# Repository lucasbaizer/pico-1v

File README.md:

# PICO 1V IS WIP

The PCB for Pico 1V is still in progress. Don't use it!

# Pico 1V

Pico 1V is an RP2040 board with the following additions/changes from the official Raspberry Pi Pico board:

* Switchable 1.8V/3.3V GPIO.
* A power LED.
* A reset button.
* A USB-C port instead of a Micro-B port.

Pico 1V is sill pin-compatible with the official Raspberry Pi Pico board, so you can use Pico 1V as a drop-in replacement for your existing Pico board.

## Acknowledgements

The schematic for Pico 1V was originally based on [Mitayi-Pico-D1](https://github.com/CIRCUITSTATE/Mitayi-Pico-D1), and the PCB for Pico 1V is from scratch.
Some of the components in the Pico 1V schematic are nearly unchanged from the Mitayi-Pico-D1 schematic.
Huge thanks to CIRCUITSTATE for open-sourcing Mitayi-Pico-D1, it was very helpful for this.

The voltage-switching implementation is based on the method described in [xenia's fantastic blog post](https://blog.awoo.systems/posts/2024-07-27-rp2040-low-voltage-operation).

## License

This project is licensed under the [MIT license](./LICENSE).

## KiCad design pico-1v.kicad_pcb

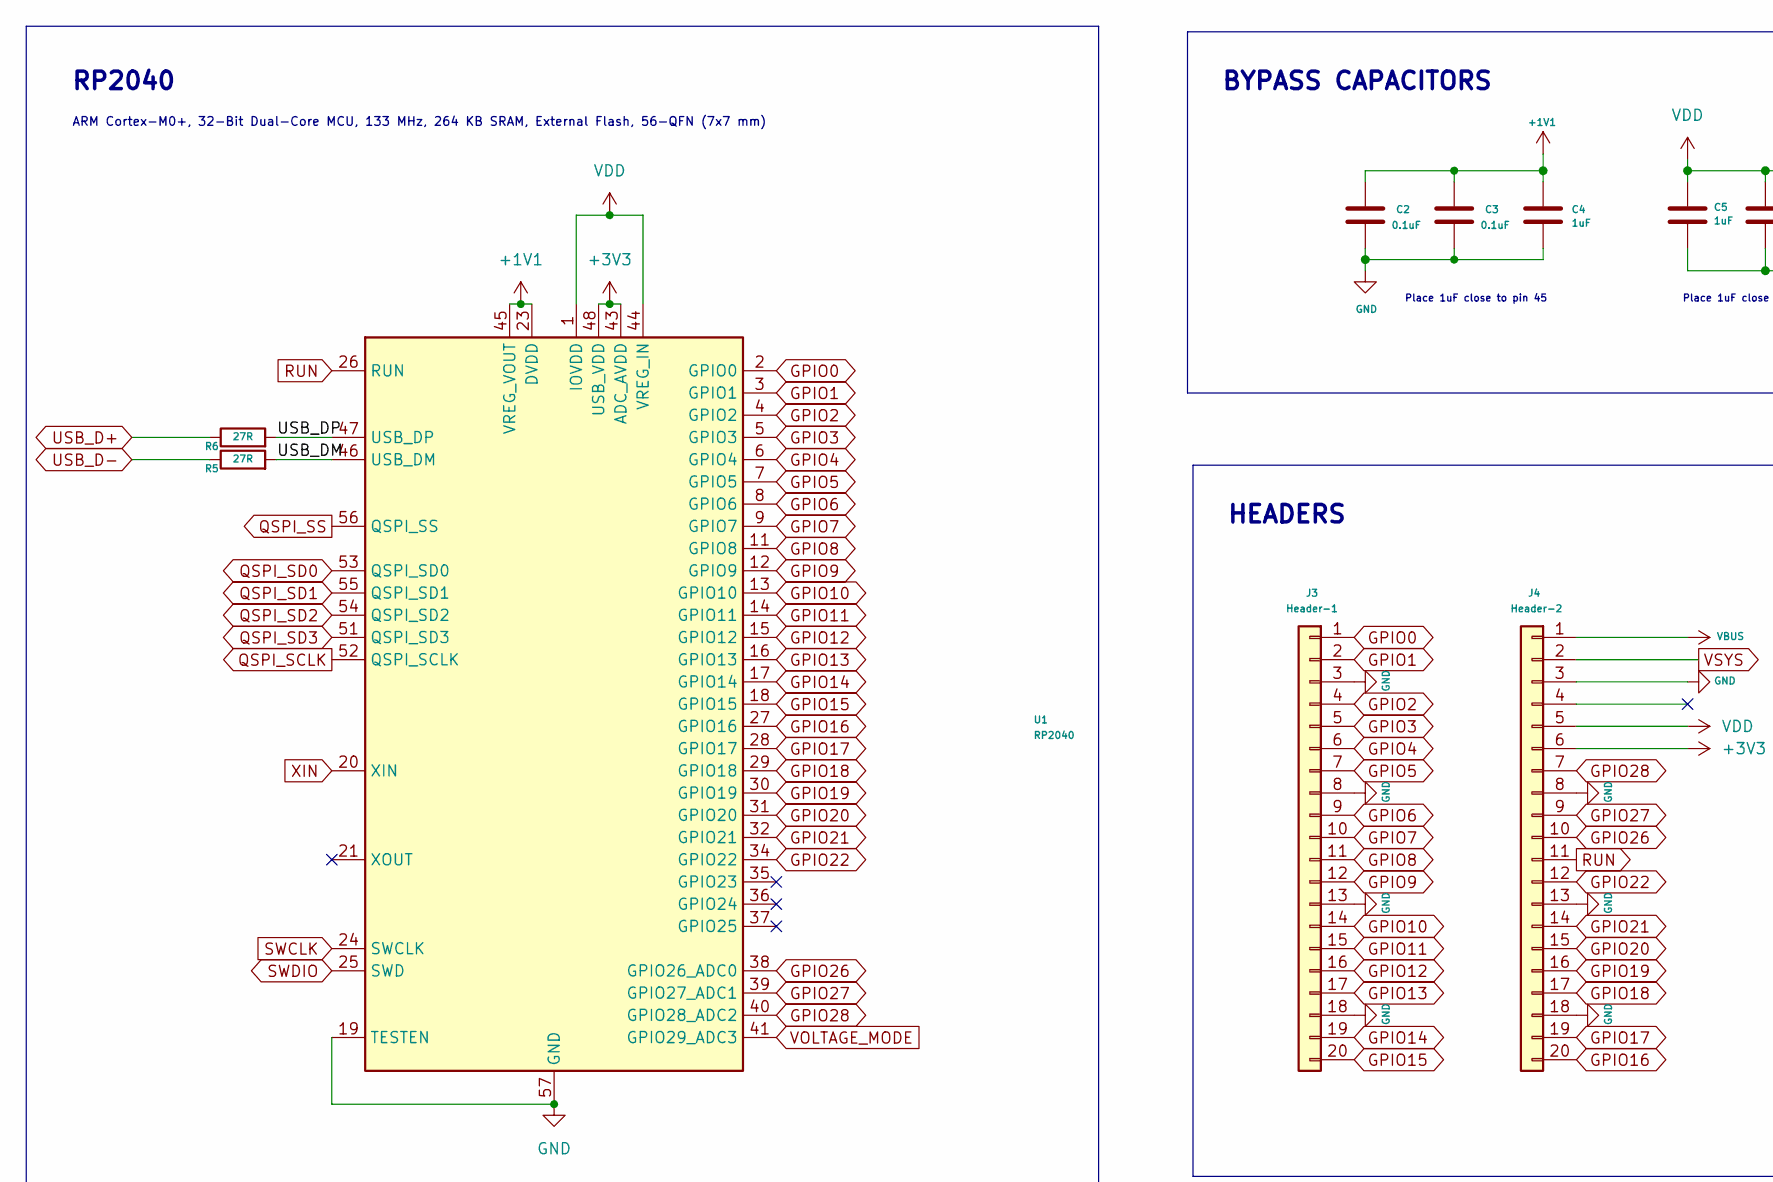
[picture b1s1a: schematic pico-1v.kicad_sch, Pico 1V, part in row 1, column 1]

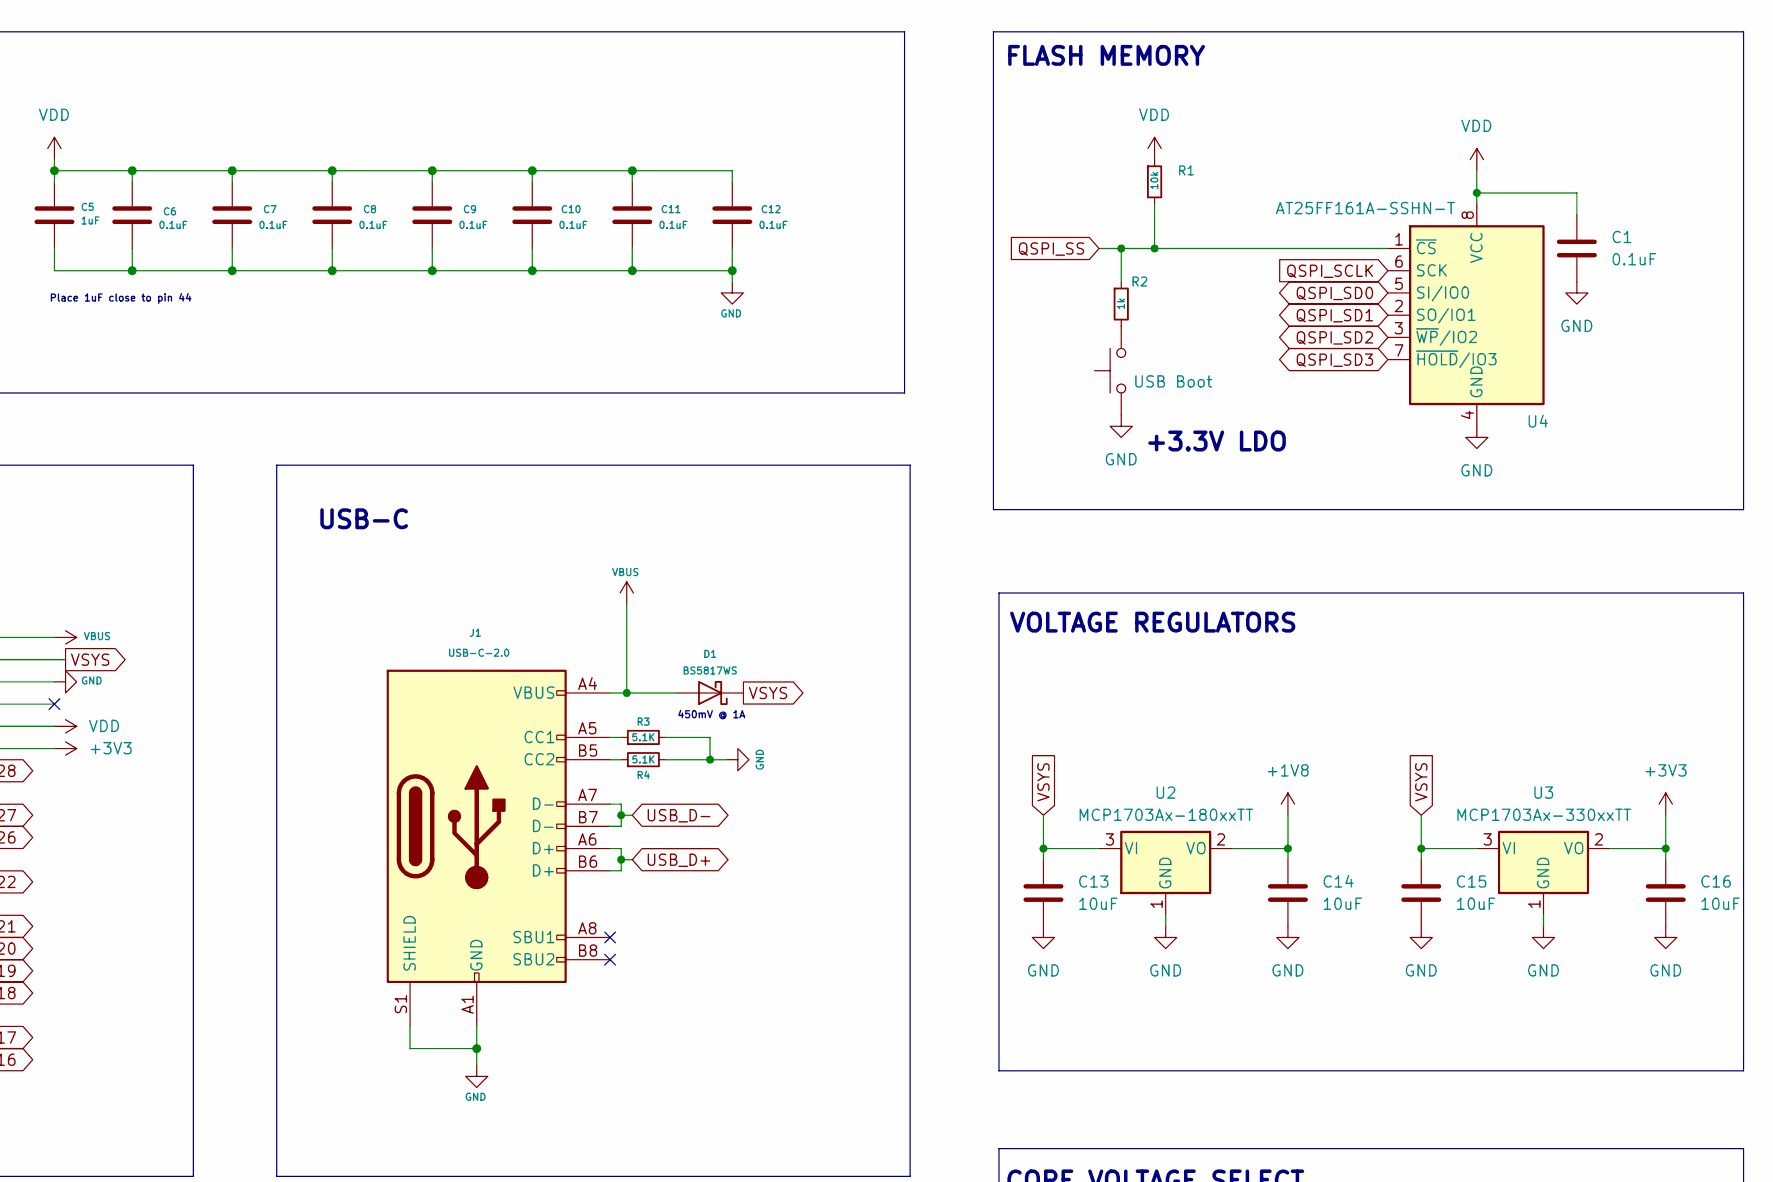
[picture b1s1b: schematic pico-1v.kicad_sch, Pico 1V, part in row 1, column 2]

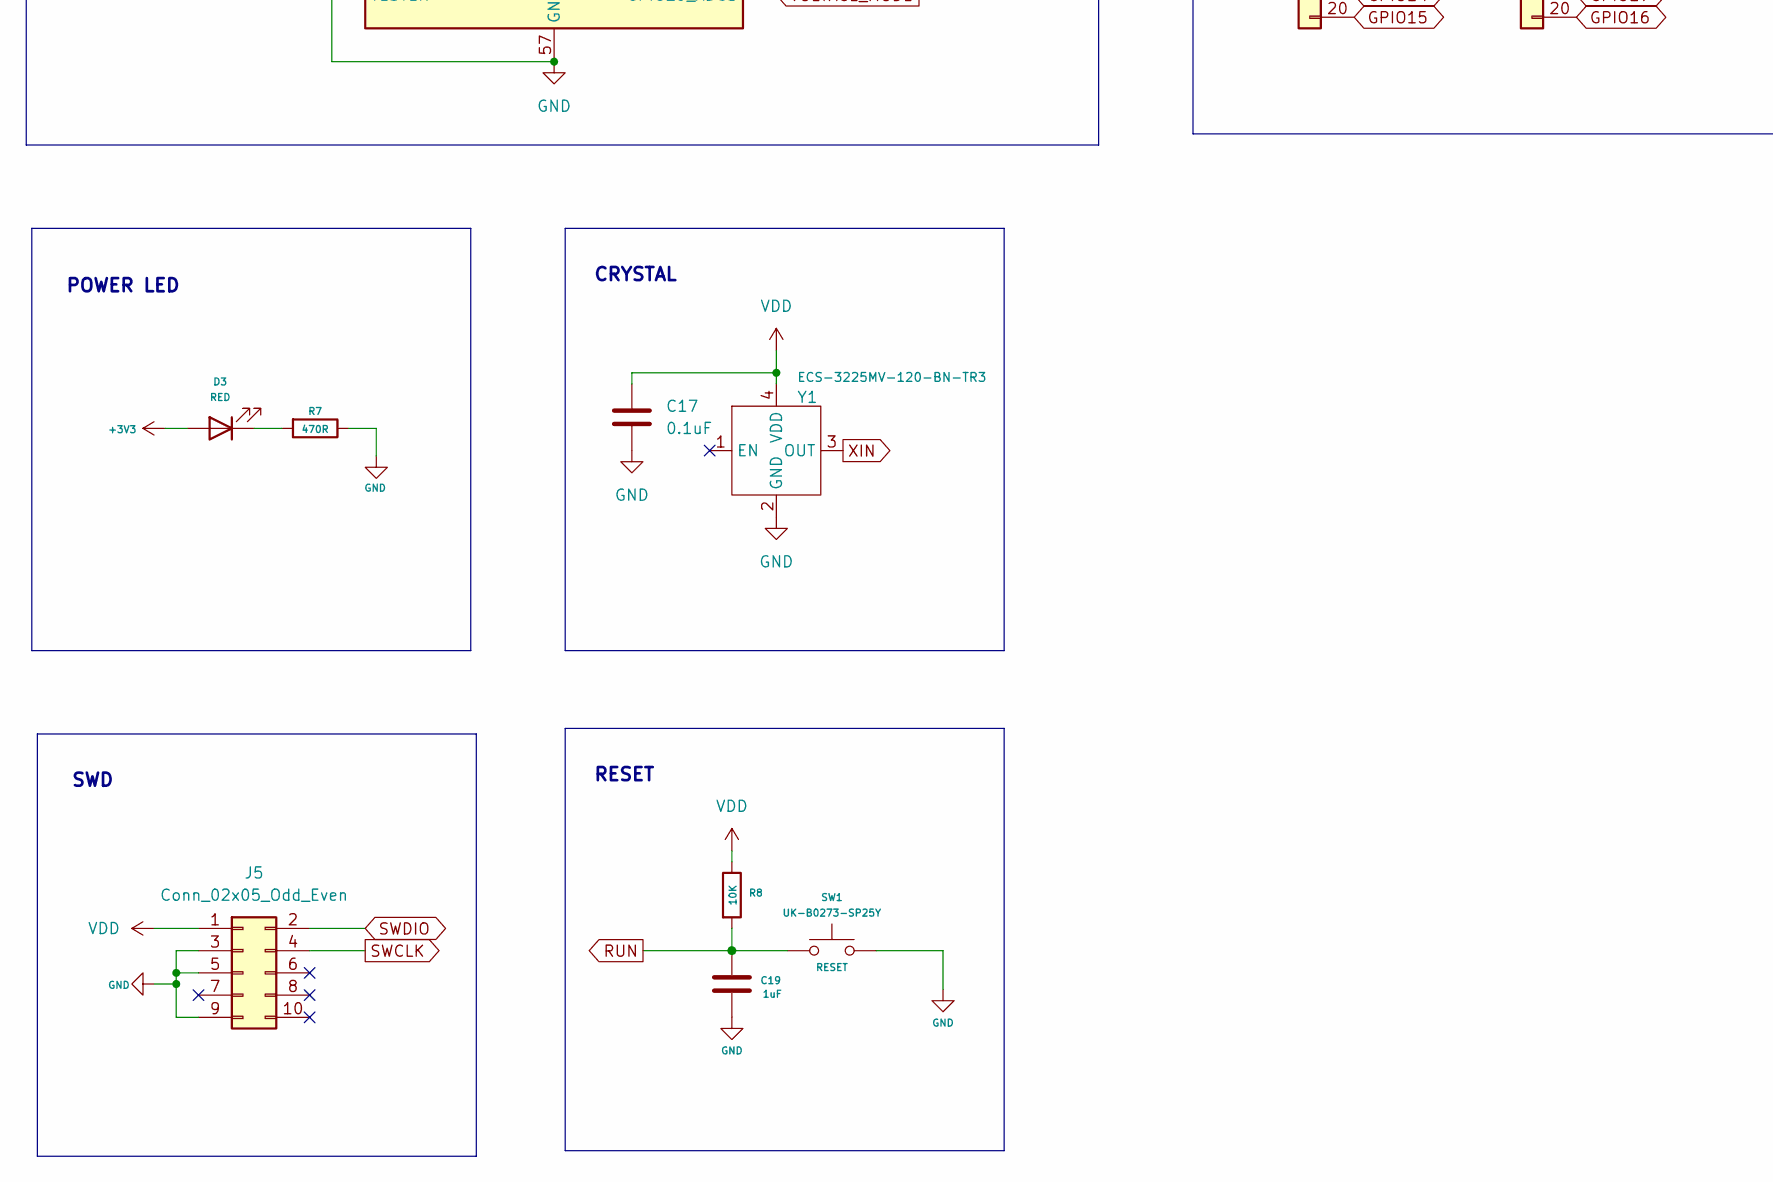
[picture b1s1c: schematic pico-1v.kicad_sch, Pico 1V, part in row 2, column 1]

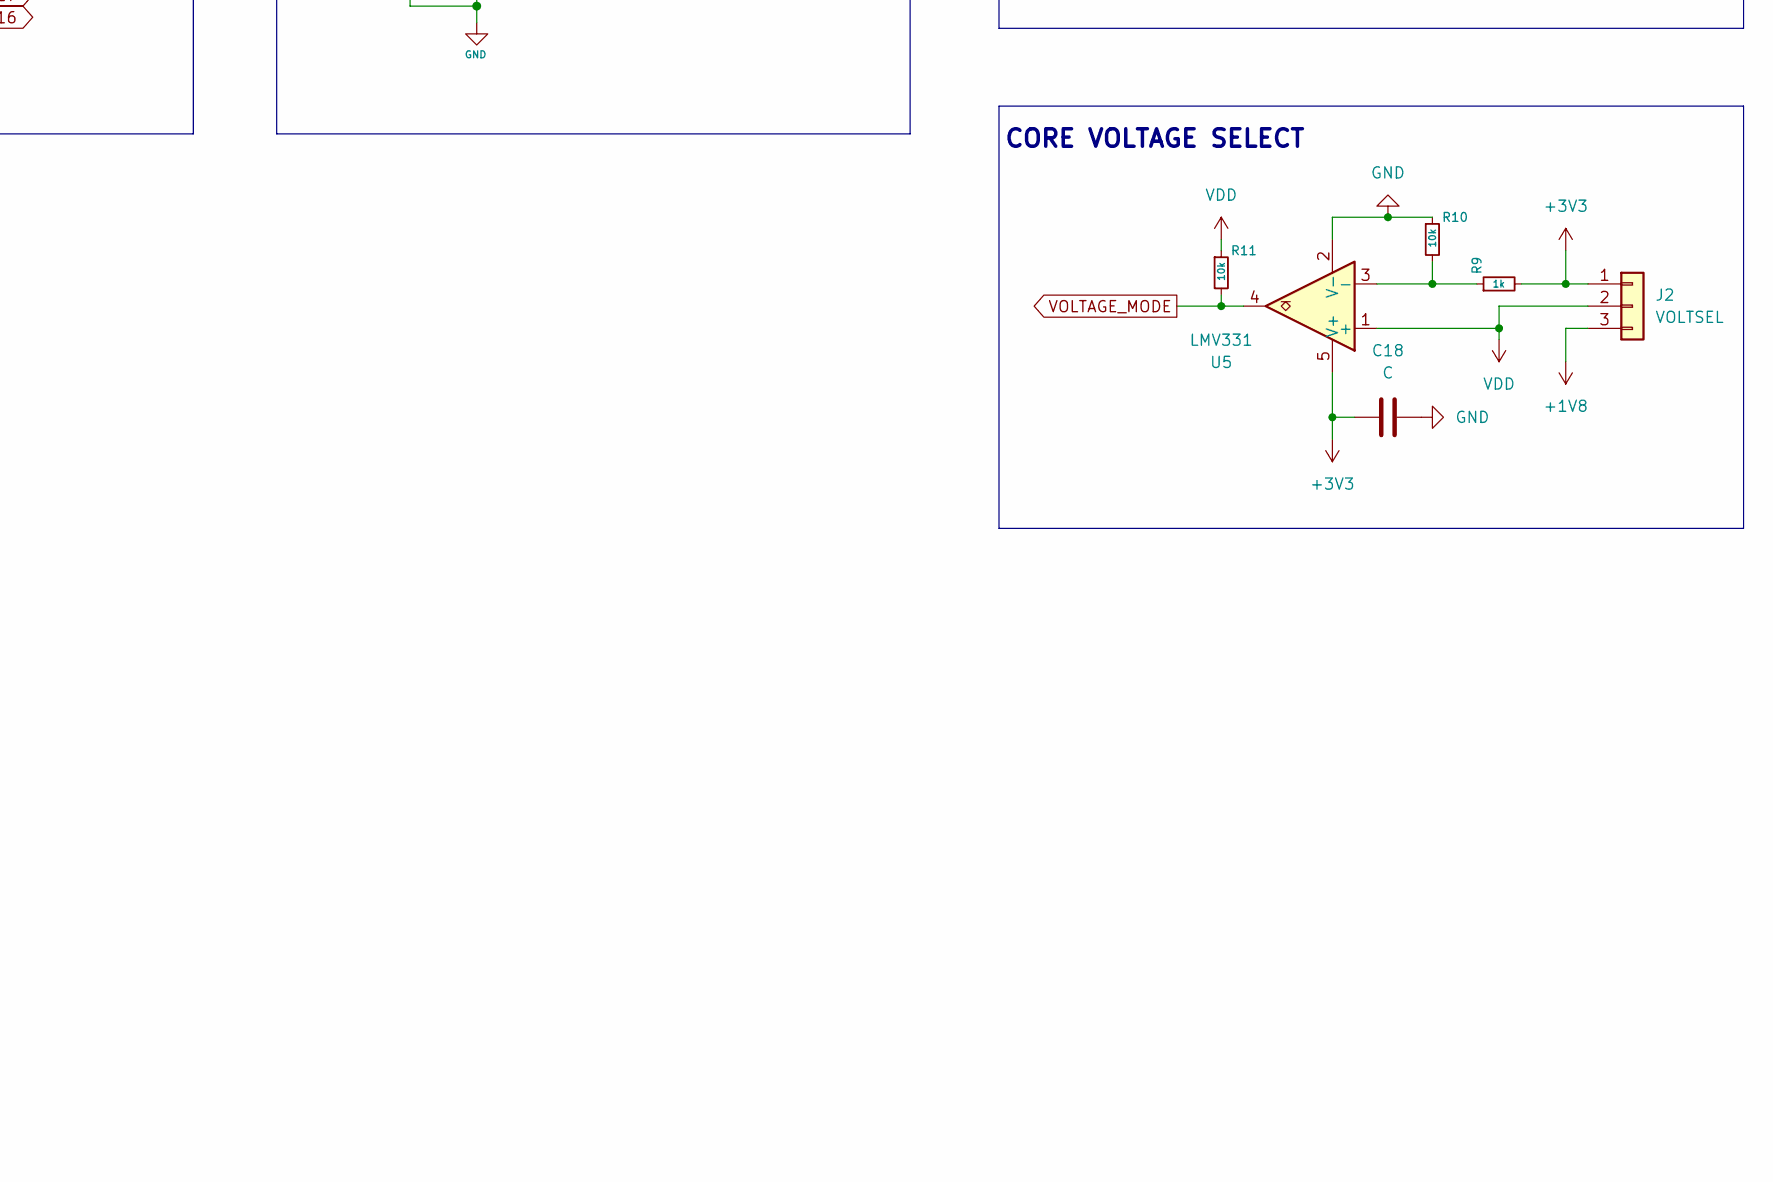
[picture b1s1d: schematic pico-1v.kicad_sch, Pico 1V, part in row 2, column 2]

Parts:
C1, C17: 0.1uF; C_0402_1005Metric
C2, C3, C6, C7, C8, C9, C10, C11, C12: 0.1uF; C_0402_1005Metric; MPN 0402B104K160CT
C4, C5, C19: 1uF; C_0402_1005Metric; MPN 0402X105K160CT
C13, C14, C15, C16: 10uF; C_0402_1005Metric
C18: C; C_0402_1005Metric
D1: BS5817WS; D_SOD-323_HandSoldering; MPN B5817WS
D3: RED; LED_0603_1608Metric; MPN 19-21SURC/S530-A2/TR8
J1: USB-C-2.0; USB_C_RECEPTACLE_31_M_12; MPN HC-TYPE-C-16P-01A
J2: VOLTSEL; PinHeader_1x03_P2.54mm_Vertical
J3: Header-1; PinHeader_1x20_P2.54mm_Vertical; MPN DNP
J4: Header-2; PinHeader_1x20_P2.54mm_Vertical; MPN DNP
J5: Conn_02x05_Odd_Even; PinHeader_2x05_P1.27mm_Vertical_SMD
R1, R10, R11: 10k; R_0402_1005Metric
R2, R9: 1k; R_0402_1005Metric
R3, R4: 5.1K; R_0402_1005Metric; MPN WR04X5101FTL
R5, R6: 27R; R_0402_1005Metric; MPN WR04X27R0FTL
R7: 470R; R_0402_1005Metric; MPN WR04X4700FTL
R8: 10K; R_0402_1005Metric; MPN WR04X1002FTL
SW1: UK-B0273-SP25Y; SW_Push_1P1T_NO_CK_KMR2; MPN UK-B0273-SP25Y
SW2: USB Boot; SW_Push_1P1T_NO_CK_KMR2
U1: RP2040; QFN-56-1EP_7x7mm_P0.4mm_EP3.2x3.2mm; MPN RP2040-B2
U2: MCP1703Ax-180xxTT; SOT-23
U3: MCP1703Ax-330xxTT; SOT-23
U4: AT25FF161A-SSHN-T; SOIC-8_3.9x4.9mm_P1.27mm
U5: LMV331; SOT-353_SC-70-5
Y1: ECS-3225MV-120-BN-TR3

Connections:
+1V1: C2.1, C3.1, C4.1, U1.23 (DVDD), U1.45 (VREG_VOUT), U1.50 (DVDD)
+1V8: C14.1, J2.3, U2.2 (VO)
+3V3: C16.1, C18.1, D3.2 (A), J2.1, J4.6, R9.2, U1.43 (ADC_AVDD), U1.48 (USB_VDD), U3.2 (VO), U5.5 (V+)
/USB_DM: R6.2, U1.46 (USB_DM)
/USB_DP: R5.2, U1.47 (USB_DP)
GND: C1.2, C2.2, C3.2, C4.2, C5.2, C6.2, C7.2, C8.2, C9.2, C10.2, C11.2, C12.2, C13.2, C14.2, C15.2, C16.2, C17.2, C18.2, C19.2, J1.A1 (GND), J1.A12 (GND), J1.B1 (GND), J1.B12 (GND), J1.S1 (SHIELD), J3.3, J3.8, J3.13, J3.18, J4.3, J4.8, J4.13, J4.18, J5.3, J5.5, J5.9, R3.2, R4.2, R7.1, R10.1, SW1.2, SW2.1, U1.19 (TESTEN), U1.57 (GND), U2.1 (GND), U3.1 (GND), U4.4 (GND), U5.2 (V-), Y1.2 (GND)
GPIO0: J3.1, U1.2 (GPIO0)
GPIO1: J3.2, U1.3 (GPIO1)
GPIO2: J3.4, U1.4 (GPIO2)
GPIO3: J3.5, U1.5 (GPIO3)
GPIO4: J3.6, U1.6 (GPIO4)
GPIO5: J3.7, U1.7 (GPIO5)
GPIO6: J3.9, U1.8 (GPIO6)
GPIO7: J3.10, U1.9 (GPIO7)
GPIO8: J3.11, U1.11 (GPIO8)
GPIO9: J3.12, U1.12 (GPIO9)
GPIO10: J3.14, U1.13 (GPIO10)
GPIO11: J3.15, U1.14 (GPIO11)
GPIO12: J3.16, U1.15 (GPIO12)
GPIO13: J3.17, U1.16 (GPIO13)
GPIO14: J3.19, U1.17 (GPIO14)
GPIO15: J3.20, U1.18 (GPIO15)
GPIO16: J4.20, U1.27 (GPIO16)
GPIO17: J4.19, U1.28 (GPIO17)
GPIO18: J4.17, U1.29 (GPIO18)
GPIO19: J4.16, U1.30 (GPIO19)
GPIO20: J4.15, U1.31 (GPIO20)
GPIO21: J4.14, U1.32 (GPIO21)
GPIO22: J4.12, U1.34 (GPIO22)
GPIO26: J4.10, U1.38 (GPIO26_ADC0)
GPIO27: J4.9, U1.39 (GPIO27_ADC1)
GPIO28: J4.7, U1.40 (GPIO28_ADC2)
unnamed: D3.1 (K), R7.2
unnamed: J1.A5 (CC1), R3.1
unnamed: J1.B5 (CC2), R4.1
unnamed: R2.2, SW2.2
unnamed: R9.1, R10.2, U5.3 (-)
QSPI_SCLK: U1.52 (QSPI_SCLK), U4.6 (SCK)
QSPI_SD0: U1.53 (QSPI_SD0), U4.5 (SI/IO0)
QSPI_SD1: U1.55 (QSPI_SD1), U4.2 (SO/IO1)
QSPI_SD2: U1.54 (QSPI_SD2), U4.3 (~WP/IO2)
QSPI_SD3: U1.51 (QSPI_SD3), U4.7 (~HOLD/IO3)
QSPI_SS: R1.2, R2.1, U1.56 (QSPI_SS), U4.1 (~CS)
RUN: C19.1, J4.11, R8.2, SW1.1, U1.26 (RUN)
SWCLK: J5.4, U1.24 (SWCLK)
SWDIO: J5.2, U1.25 (SWD)
USB_D+: J1.A6 (D+), J1.B6 (D+), R5.1
USB_D-: J1.A7 (D-), J1.B7 (D-), R6.1
VBUS: D1.2 (A), J1.A4 (VBUS), J1.A9 (VBUS), J1.B4 (VBUS), J1.B9 (VBUS), J4.1
VDD: C1.1, C5.1, C6.1, C7.1, C8.1, C9.1, C10.1, C11.1, C12.1, C17.1, J2.2, J4.5, J5.1, R1.1, R8.1, R11.1, U1.1 (IOVDD), U1.10 (IOVDD), U1.22 (IOVDD), U1.33 (IOVDD), U1.42 (IOVDD), U1.44 (VREG_IN), U1.49 (IOVDD), U4.8 (VCC), U5.1 (+), Y1.4 (VDD)
VOLTAGE_MODE: R11.2, U1.41 (GPIO29_ADC3), U5.4
VSYS: C13.1, C15.1, D1.1 (K), J4.2, U2.3 (VI), U3.3 (VI)
XIN: U1.20 (XIN), Y1.3 (OUT)

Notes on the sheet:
CORE VOLTAGE SELECT
HEADERS
+3.3V LDO
450mV @ 1A
POWER LED
Place 1uF close to pin 45
RP2040
FLASH MEMORY
SWD
RESET
Place 1uF close to pin 44
CRYSTAL
VOLTAGE REGULATORS
BYPASS CAPACITORS
USB-C
ARM Cortex-M0+, 32-Bit Dual-Core MCU, 133 MHz, 264 KB SRAM, External Flash, 56-QFN (7x7 mm)

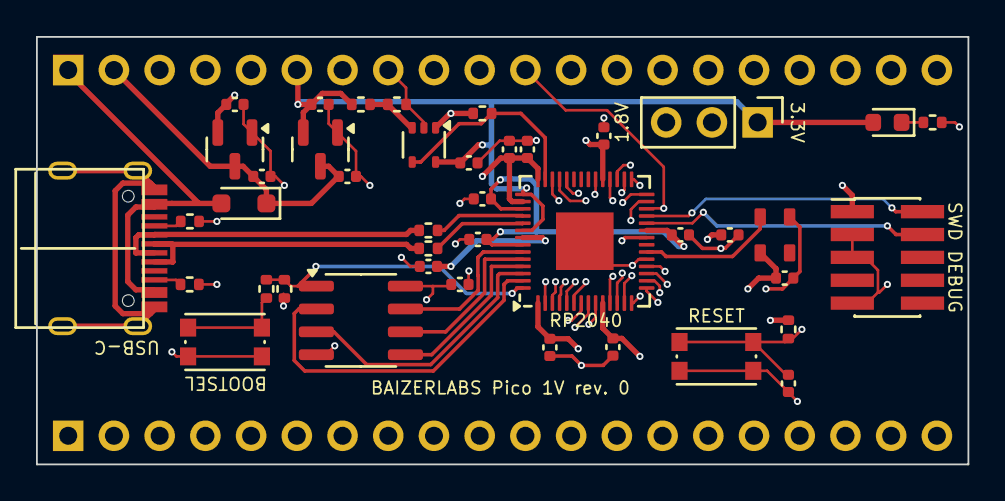
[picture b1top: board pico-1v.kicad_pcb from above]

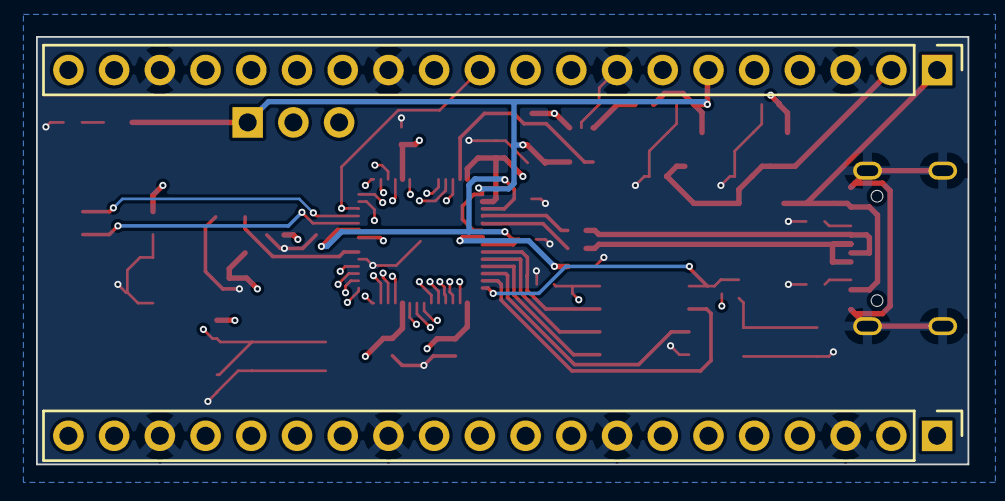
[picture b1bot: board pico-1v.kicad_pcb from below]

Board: 4 copper layers, 51.8 x 23.8 mm, 44 parts (2 on the bottom side), 53 nets.

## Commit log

2025-08-22 Initial Pico 1V commit
2025-08-22 License + Readme
2025-08-22 More improvements to schematic
2025-08-22 Schematic fixes
2025-08-22 Updated some stuff
2025-08-25 Rev 1 PCB
2025-08-29 Fixed for production
2025-08-29 More stuff
2025-08-31 Various fixes
